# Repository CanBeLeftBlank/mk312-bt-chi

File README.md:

Welcome to the MK-312BTχ (Chi) project. This is a fork of the project bij [CrashOverride85](https://github.com/CrashOverride85/mk312-bt) which itself is cloned from an earlier project and ultimately a project by MetaFetish that has since been removed from GitHub.

# What is it?

MK-312BTχ is a DYI electronics kit to build an Estim box, including schematics, printed circuit board layouts and parts lists. If you don't know what an Estim box is or have no experience with electronics and soldering, this project is probably not for you...

If you do know what an Estim box is: build and use at your own risk! Even though a lot of people have build these devices there's always room for error and (painful) experiences.

## How is this different from the other cloned projects?

The original designs were made with the Eagle CAD software. Since I don't have an expensive Eagle license I decided to convert the schematics to the open source KiCad format. This will hopefully allow more people to experiment with this or improve the design.

There was also an update available of the schematic (v1.4) and final board design, but only as PDFs and images. So I compared them with the old v1.3 Eagle designs and re-applied the changes in the KiCad version. This is the original v1.4χ version.

Second, documentation was always a bit lacking or confusing. This project aims to improve on that.

And who knows, maybe in the future we'll have original source code and firmware as well...

## What's with the X in the version?

It's not an X but the Greek letter χ (Chi) which is pronounced 'Kai', similar to 'KiCad'. 

# Building!

So, let's get to the main event. There are 4 parts to this:

* Getting the circuit boards
* Buying the electronic parts
* Soldering and putting it together
* Programming the firmware

Oh yes, before you continue: you must be able to program an Atmel microcontroller or have someone who can do it for you. 

## Circuit boards (PCB)

In the gerbers/ folder are the latest Gerber files as zip files, one for each of the 3 boards: the main circuit board, the display print and the front panel. Easiest is to have these boards made at a PCB factory; the front panel looks best with a black soldermask.

The zip files contain Gerber files with Protel filenames; they are known to work with at least one PCB manufacturer (PCBWay: no affiliation or sponsorship). I would like some feedback on how it fares with other manufacturers.

## The electronic parts

*As of the time of writing (December 2022), there is still a global shortage of chips and other electronic parts. However, with a little bit of creativity you can still get all the parts. For example I substituted the main processor, an ATMega16A-PU, with the ATMega16L-8PU, a low-power version that runs 'only' at 8 MHz which so happens to be the actual clockspeed. The stereo pot at the display panel is no longer available at Mouser, but AliExpress has plenty of them. And the blue LCD that is originally specified is not shipped everywhere, so I picked a green one.*

In the bom_and_info/ folder is a spreadsheet with a parts-list for Mouser; a few substitutions / replacements have been marked with colors and notes. This list has been used to get parts in August 2022, but your milage may vary. There is no BOM for other parts suppliers, but all components are standard parts so it should be easy to find them. The BOM also contains a suitable case.

There is one choice you have to make: which transformer to use. The PCB supports two types: the Xicon 42TL004 (default) and the 42TU200. The latter is bigger and should give more power on the outputs, but was until recently only available in bulk. If you buy the 42TU200 you must use a lower value for R30; see the BOM for details.

You need a short ribbon cable to connect the display to the main board. The BOM lists separate components for this but you can also buy a pre-made 24-pin ribbon cable at Amazon, EBay or AliExpress.

## Building it

In the bom_and_info/ folder there is a document with detailed building instructions, as well as 2 PDFs with component placements for the display and mainboard. You will need a soldering iron with a fine tip, some thin solder (leaded or lead-free) and a bit of free time. All parts are through-hole so easy to mount. 

With the given PCBs and case you can mount the mainboard at the bottom of the case with a few short screws; the display with front panel slides in vertically (see the images). 

## Programming the firmware

This is a bit of a gray area. There are various firmware revisions floating around on the 'Net, sometimes with names like 'buttshock'; problem is they are only available as binary files, no sources. Some have patches and fixes to the original firmware but are still binary-only. 

This repository contains an old but working version of the firmware with tweaks for the chosen LCD; this has to do with the ← and → symbols on the LCD that differs between brands.

To set your programmer fuses:

* Low fuse: 0xFF
* High fuse: 0xDC

This assumes an 8 MHz crystal is used.

On the mainboard PCB is a 6-pin header for programming, compatible with the Atmel-ICE programmer (and probably a few others). An alternative is an external programmer. There is no way to upload the firmware using a bootloader AFAIK.

# Using it

## Charging

The recommende charging voltage is 15 Volt DC; the box monitors the input voltage and if it is too high, the firmware may display an error 21. The battery will still be charged to its nominal voltage but the LM2914 might get hot due to a high charging current.

Note: as with all estim boxes it is not recommend to use the machine while it is being charged and thus (indirectly) connected to mains voltage.

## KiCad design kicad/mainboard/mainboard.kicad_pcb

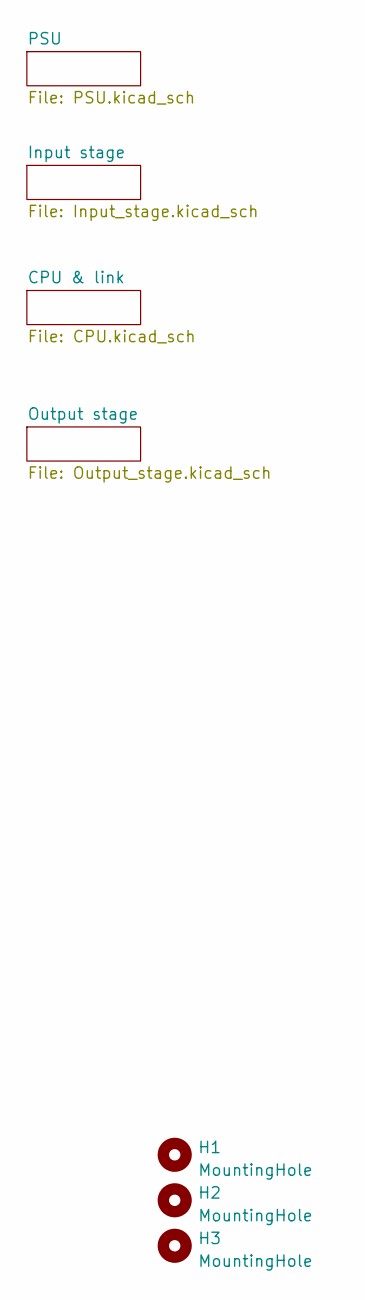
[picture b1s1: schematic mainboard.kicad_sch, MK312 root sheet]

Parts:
H1, H2, H3: MountingHole; MountingHole_2.5mm

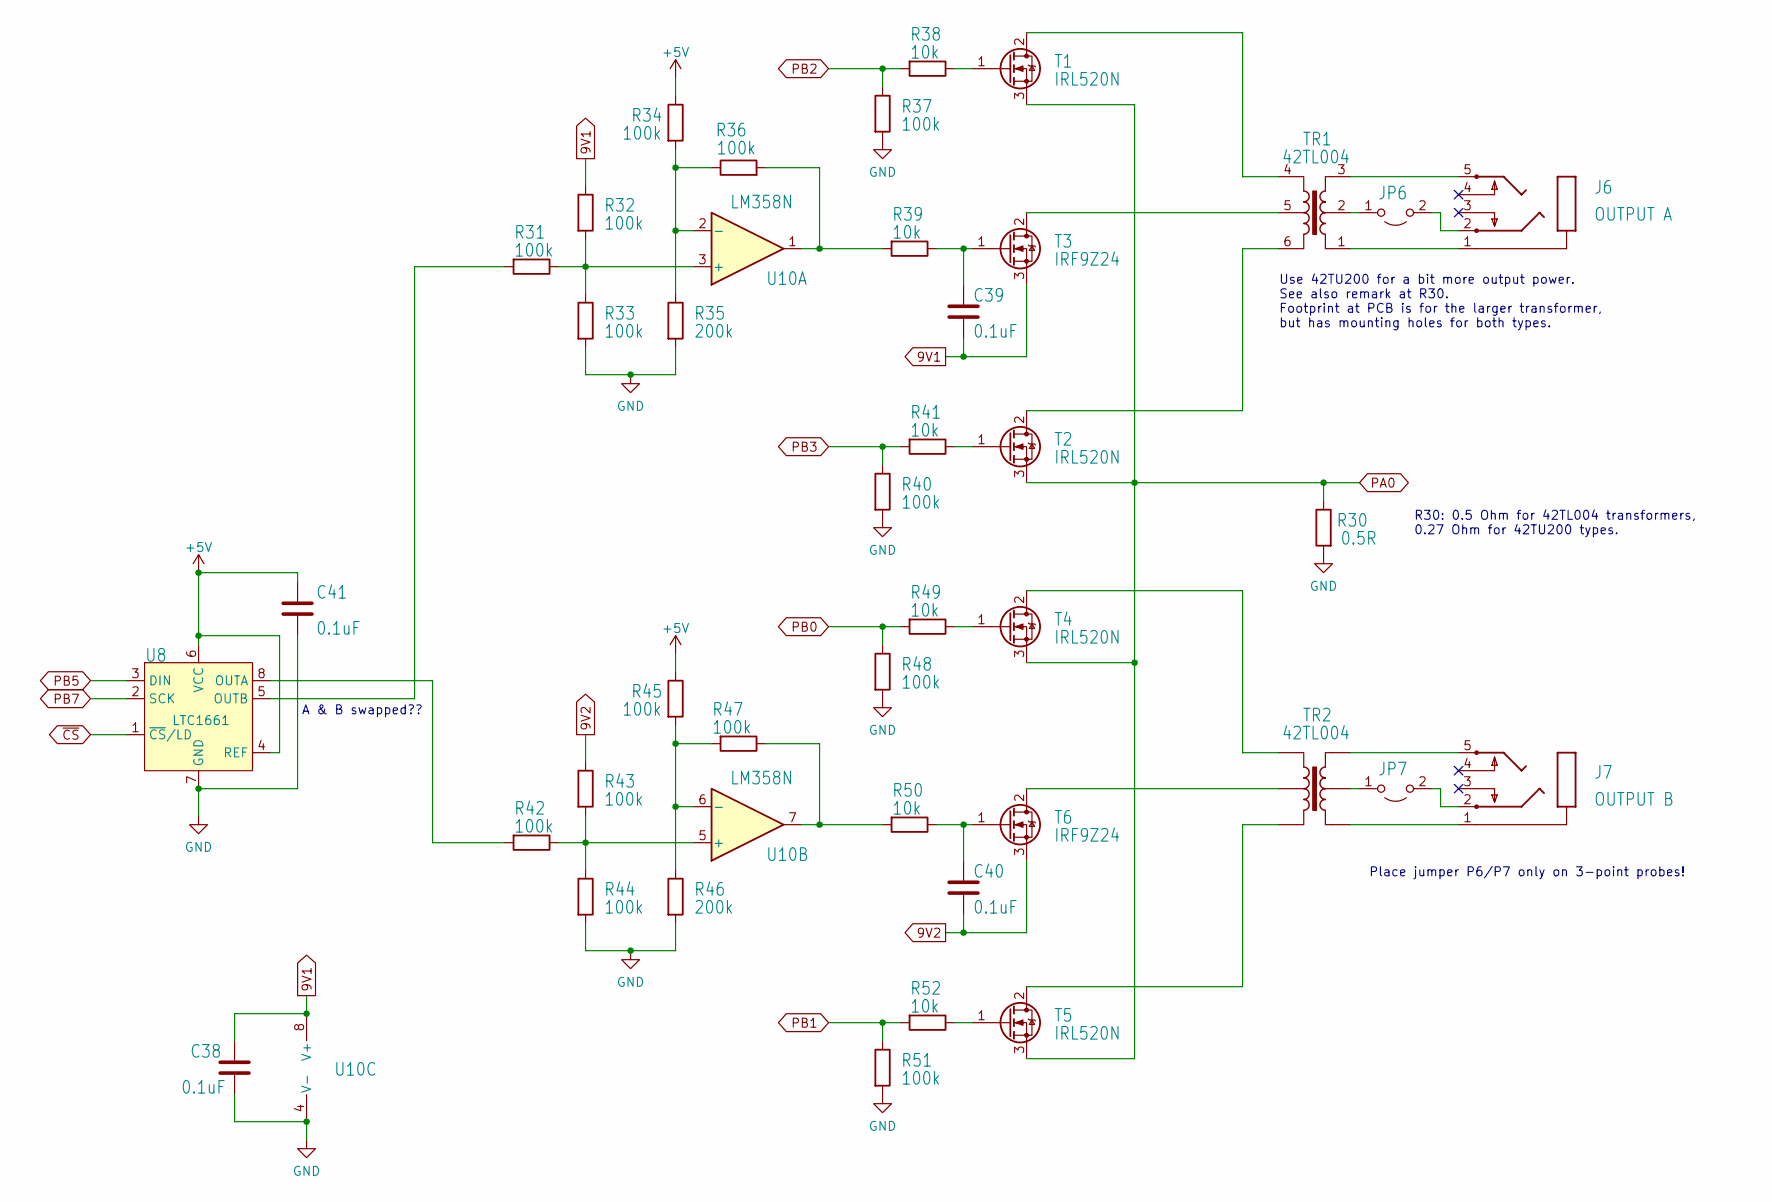
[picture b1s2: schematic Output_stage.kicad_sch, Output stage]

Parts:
C38, C39, C40, C41: 0.1uF; C_Disc_D3.0mm_W1.6mm_P2.50mm
J6: OUTPUT A; STX3100
J7: OUTPUT B; STX3100
JP6, JP7: JP1E; PinHeader_1x02_P2.54mm_Vertical
R30: 0.5R; R_Axial_DIN0309_L9.0mm_D3.2mm_P12.70mm_Horizontal
R31, R32, R33, R34, R36, R42, R43, R44, R45, R47: 100k; R_Axial_DIN0207_L6.3mm_D2.5mm_P10.16mm_Horizontal
R35, R46: 200k; R_Axial_DIN0207_L6.3mm_D2.5mm_P10.16mm_Horizontal
R37, R40, R48, R51: 100k; R_Axial_DIN0207_L6.3mm_D2.5mm_P2.54mm_Vertical
R38, R41, R49, R52: 10k; R_Axial_DIN0207_L6.3mm_D2.5mm_P2.54mm_Vertical
R39, R50: 10k; R_Axial_DIN0207_L6.3mm_D2.5mm_P10.16mm_Horizontal
T1, T2, T4, T5: IRL520N; TO-220-3_Vertical
T3, T6: IRF9Z24; TO-220-3_Vertical
TR1, TR2: 42TL004; Transformer_Xicon_42TL_42TU_Combi
U8: LTC1661; DIP-8_W7.62mm
U10: LM358N; DIP-8_W7.62mm

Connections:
9V1: C38.1, C39.2, R32.1, T3.3 (S), U10.8 (V+); also elsewhere on the board
9V2: C40.2, R43.1, T6.3 (S); also elsewhere on the board
+5V: C41.1, R34.1, R45.1, U8.4 (REF), U8.6 (VCC); also elsewhere on the board
GND: C38.2, C41.2, R30.2, R33.2, R35.2, R37.2, R40.2, R44.2, R46.2, R48.2, R51.2, U8.7 (GND), U10.4 (V-); also elsewhere on the board
unnamed: C39.1, R39.1, T3.1 (G)
unnamed: C40.1, R50.1, T6.1 (G)
unnamed: J6.1, TR1.1
unnamed: J6.2, JP6.2 (B)
unnamed: J6.5, TR1.3
unnamed: J7.1, TR2.1
unnamed: J7.2, JP7.2 (B)
unnamed: J7.5, TR2.3
unnamed: JP6.1 (A), TR1.2
unnamed: JP7.1 (A), TR2.2
unnamed: R31.1, R32.2, R33.1, U10.3 (+)
unnamed: R31.2, U8.5 (OUTB)
unnamed: R34.2, R35.1, R36.1, U10.2 (-)
unnamed: R36.2, R39.2, U10.1
unnamed: R38.1, T1.1 (G)
unnamed: R41.1, T2.1 (G)
unnamed: R42.1, R43.2, R44.1, U10.5 (+)
unnamed: R42.2, U8.8 (OUTA)
unnamed: R45.2, R46.1, R47.2, U10.6 (-)
unnamed: R47.1, R50.2, U10.7
unnamed: R49.1, T4.1 (G)
unnamed: R52.1, T5.1 (G)
unnamed: T1.2 (D), TR1.4
unnamed: T2.2 (D), TR1.6
unnamed: T3.2 (D), TR1.5
unnamed: T4.2 (D), TR2.4
unnamed: T5.2 (D), TR2.6
unnamed: T6.2 (D), TR2.5
PA0: R30.1, T1.3 (S), T2.3 (S), T4.3 (S), T5.3 (S); also elsewhere on the board
PB0: R48.1, R49.2; also elsewhere on the board
PB1: R51.1, R52.2; also elsewhere on the board
PB2: R37.1, R38.2; also elsewhere on the board
PB3: R40.1, R41.2; also elsewhere on the board
PB5: U8.3 (DIN); also elsewhere on the board
PB7: U8.2 (SCK); also elsewhere on the board
~CS: U8.1 (~CS/LD); also elsewhere on the board

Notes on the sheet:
A & B swapped??
R30: 0.5 Ohm for 42TL004 transformers, 0.27 Ohm for 42TU200 types.
Use 42TU200 for a bit more output power. See also remark at R30. Footprint at PCB is for the larger transformer, but has mounting holes for both types.
Place jumper P6/P7 only on 3-point probes!

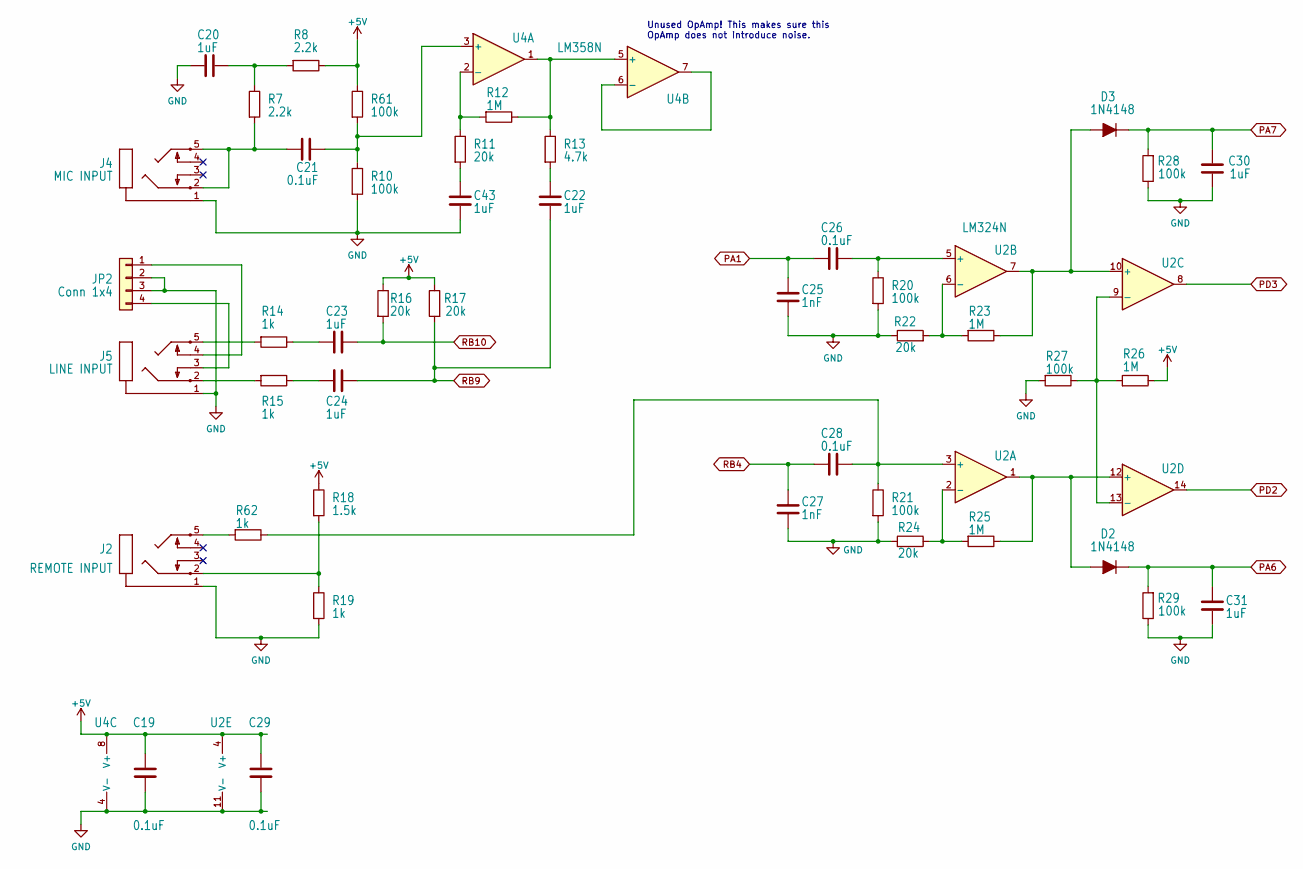
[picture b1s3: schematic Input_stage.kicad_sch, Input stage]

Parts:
C19, C21, C26, C28, C29: 0.1uF; C_Disc_D3.0mm_W1.6mm_P2.50mm
C20, C22, C23, C24, C30, C31, C43: 1uF; C_Disc_D3.4mm_W2.1mm_P2.50mm
C25, C27: 1nF; C_Disc_D3.0mm_W1.6mm_P2.50mm
D2, D3: 1N4148; D_DO-35_SOD27_P10.16mm_Horizontal
J2: REMOTE INPUT; STX3100
J4: MIC INPUT; STX3100
J5: LINE INPUT; STX3100
JP2: Conn 1x4; PinHeader_1x04_P2.54mm_Vertical
R7, R8: 2.2k; R_Axial_DIN0207_L6.3mm_D2.5mm_P10.16mm_Horizontal
R10, R20, R21, R27, R28, R29, R61: 100k; R_Axial_DIN0207_L6.3mm_D2.5mm_P10.16mm_Horizontal
R11, R16, R17, R22, R24: 20k; R_Axial_DIN0207_L6.3mm_D2.5mm_P10.16mm_Horizontal
R12, R23, R25, R26: 1M; R_Axial_DIN0207_L6.3mm_D2.5mm_P10.16mm_Horizontal
R13: 4.7k; R_Axial_DIN0207_L6.3mm_D2.5mm_P10.16mm_Horizontal
R14, R15, R19, R62: 1k; R_Axial_DIN0207_L6.3mm_D2.5mm_P10.16mm_Horizontal
R18: 1.5k; R_Axial_DIN0207_L6.3mm_D2.5mm_P10.16mm_Horizontal
U2: LM324N; DIP-14_W7.62mm
U4: LM358N; DIP-8_W7.62mm

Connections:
+5V: C19.1, C29.1, R8.1, R16.1, R17.1, R18.1, R26.1, R61.1, U2.4 (V+), U4.8 (V+); also elsewhere on the board
GND: C19.2, C20.2, C25.1, C27.1, C29.2, C30.1, C31.2, C43.2, J2.1, J4.1, J5.1, JP2.2, JP2.3, R10.2, R19.2, R20.2, R21.2, R22.1, R24.2, R27.2, R28.1, R29.1, U2.11 (V-), U4.4 (V-); also elsewhere on the board
unnamed: C20.1, R7.1, R8.2
unnamed: C21.1, J4.2, J4.5, R7.2
unnamed: C21.2, R10.1, R61.2, U4.3 (+)
unnamed: C22.1, R13.2
unnamed: C23.2, R14.1
unnamed: C24.2, R15.1
unnamed: C26.1, R20.1, U2.5 (+)
unnamed: C28.1, R21.1, R62.1, U2.3 (+)
unnamed: C43.1, R11.2
unnamed: D2.2 (A), R25.1, U2.1, U2.12 (+)
unnamed: D3.2 (A), R23.1, U2.7, U2.10 (+)
unnamed: J2.2, R18.2, R19.1
unnamed: J2.5, R62.2
unnamed: J5.2, R15.2
unnamed: J5.3, JP2.4
unnamed: J5.4, JP2.1
unnamed: J5.5, R14.2
unnamed: R11.1, R12.2, U4.2 (-)
unnamed: R12.1, R13.1, U4.1, U4.5 (+)
unnamed: R22.2, R23.2, U2.6 (-)
unnamed: R24.1, R25.2, U2.2 (-)
unnamed: R26.2, R27.1, U2.9 (-), U2.13 (-)
unnamed: U4.6 (-), U4.7
PA1: C25.2, C26.2; also elsewhere on the board
PA6: C31.1, D2.1 (K), R29.2; also elsewhere on the board
PA7: C30.2, D3.1 (K), R28.2; also elsewhere on the board
PD2: U2.14; also elsewhere on the board
PD3: U2.8; also elsewhere on the board
RB4: C27.2, C28.2; also elsewhere on the board
RB9: C22.2, C24.1, R17.2; also elsewhere on the board
RB10: C23.1, R16.2; also elsewhere on the board

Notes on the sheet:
Unused OpAmp! This makes sure this OpAmp does not introduce noise.

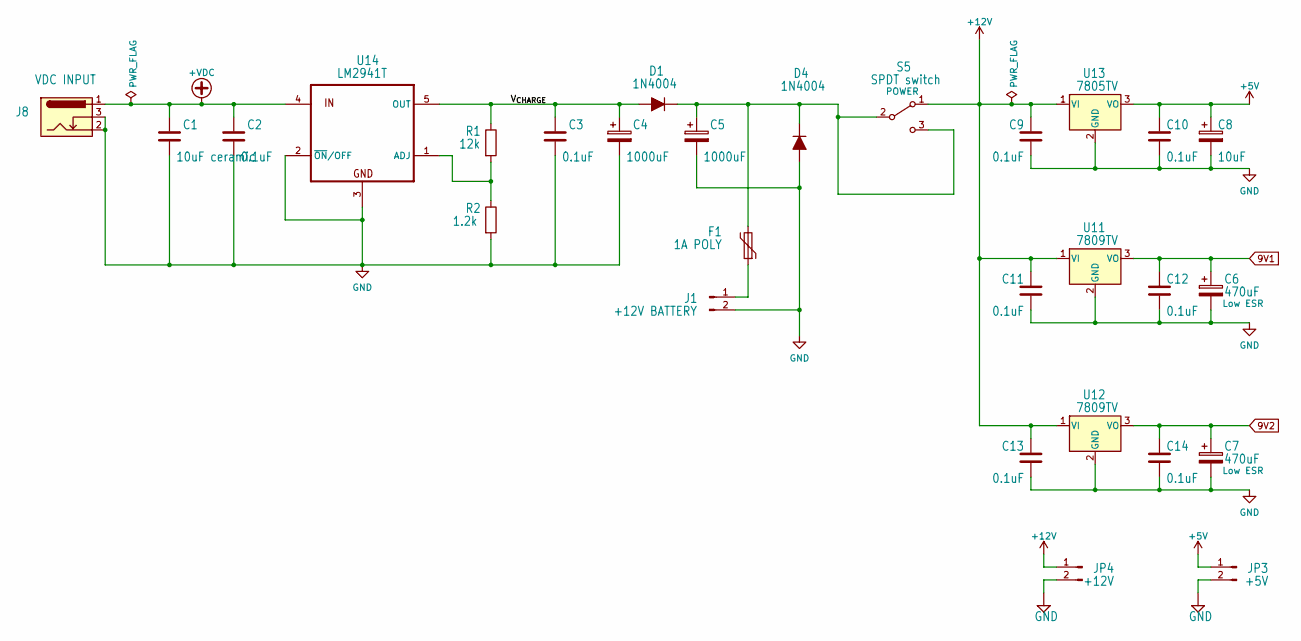
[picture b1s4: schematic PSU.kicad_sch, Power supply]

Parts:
C1: 10uF ceramic; C_Disc_D5.0mm_W2.5mm_P2.50mm
C2, C3, C9, C10, C11, C12, C13, C14: 0.1uF; C_Disc_D3.0mm_W1.6mm_P2.50mm
C4, C5: 1000uF; CP_Radial_D10.0mm_P5.00mm
C6, C7: 470uF; CP_Radial_D8.0mm_P3.50mm
C8: 10uF; CP_Radial_D6.3mm_P2.50mm
D1, D4: 1N4004; D_DO-41_SOD81_P10.16mm_Horizontal
F1: 1A POLY; Fuse_Littelfuse-LVR100
J1: +12V BATTERY; DEANS
J8: VDC INPUT; BarrelJack_GCT_DCJ200-10-A_Horizontal
JP3: +5V; PinHeader_1x02_P2.54mm_Vertical
JP4: +12V; PinHeader_1x02_P2.54mm_Vertical
R1: 12k; R_Axial_DIN0207_L6.3mm_D2.5mm_P10.16mm_Horizontal
R2: 1.2k; R_Axial_DIN0207_L6.3mm_D2.5mm_P10.16mm_Horizontal
S5: SPDT switch; LPV-1
U11, U12: 7809TV; TO-220-3_Vertical
U13: 7805TV; TO-220-3_Vertical
U14: LM2941T; TO-220-5_P3.4x3.7mm_StaggerOdd_Lead3.8mm_Vertical

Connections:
9V1: C6.1, C12.1, U11.3 (VO); also elsewhere on the board
9V2: C7.1, C14.1, U12.3 (VO); also elsewhere on the board
+5V: C8.1, C10.1, JP3.1, U13.3 (VO); also elsewhere on the board
+12V: C9.1, C11.1, C13.1, JP4.1, S5.1 (A), U11.1 (VI), U12.1 (VI), U13.1 (VI); also elsewhere on the board
+VDC: C1.1, C2.1, J8.1, U14.4 (IN); also elsewhere on the board
/PSU/V_{CHARGE}: C3.1, C4.1, D1.2 (A), R1.1, U14.5 (OUT)
GND: C1.2, C2.2, C3.2, C4.2, C5.2, C6.2, C7.2, C8.2, C9.2, C10.2, C11.2, C12.2, C13.2, C14.2, D4.2 (A), J1.2, J8.2, J8.3, JP3.2, JP4.2, R2.2, U11.2 (GND), U12.2 (GND), U13.2 (GND), U14.2 (~ON/OFF), U14.3 (GND); also elsewhere on the board
unnamed: C5.1, D1.1 (K), D4.1 (K), F1.2, S5.2 (B), S5.3 (C)
unnamed: F1.1, J1.1
unnamed: R1.2, R2.1, U14.1 (ADJ)

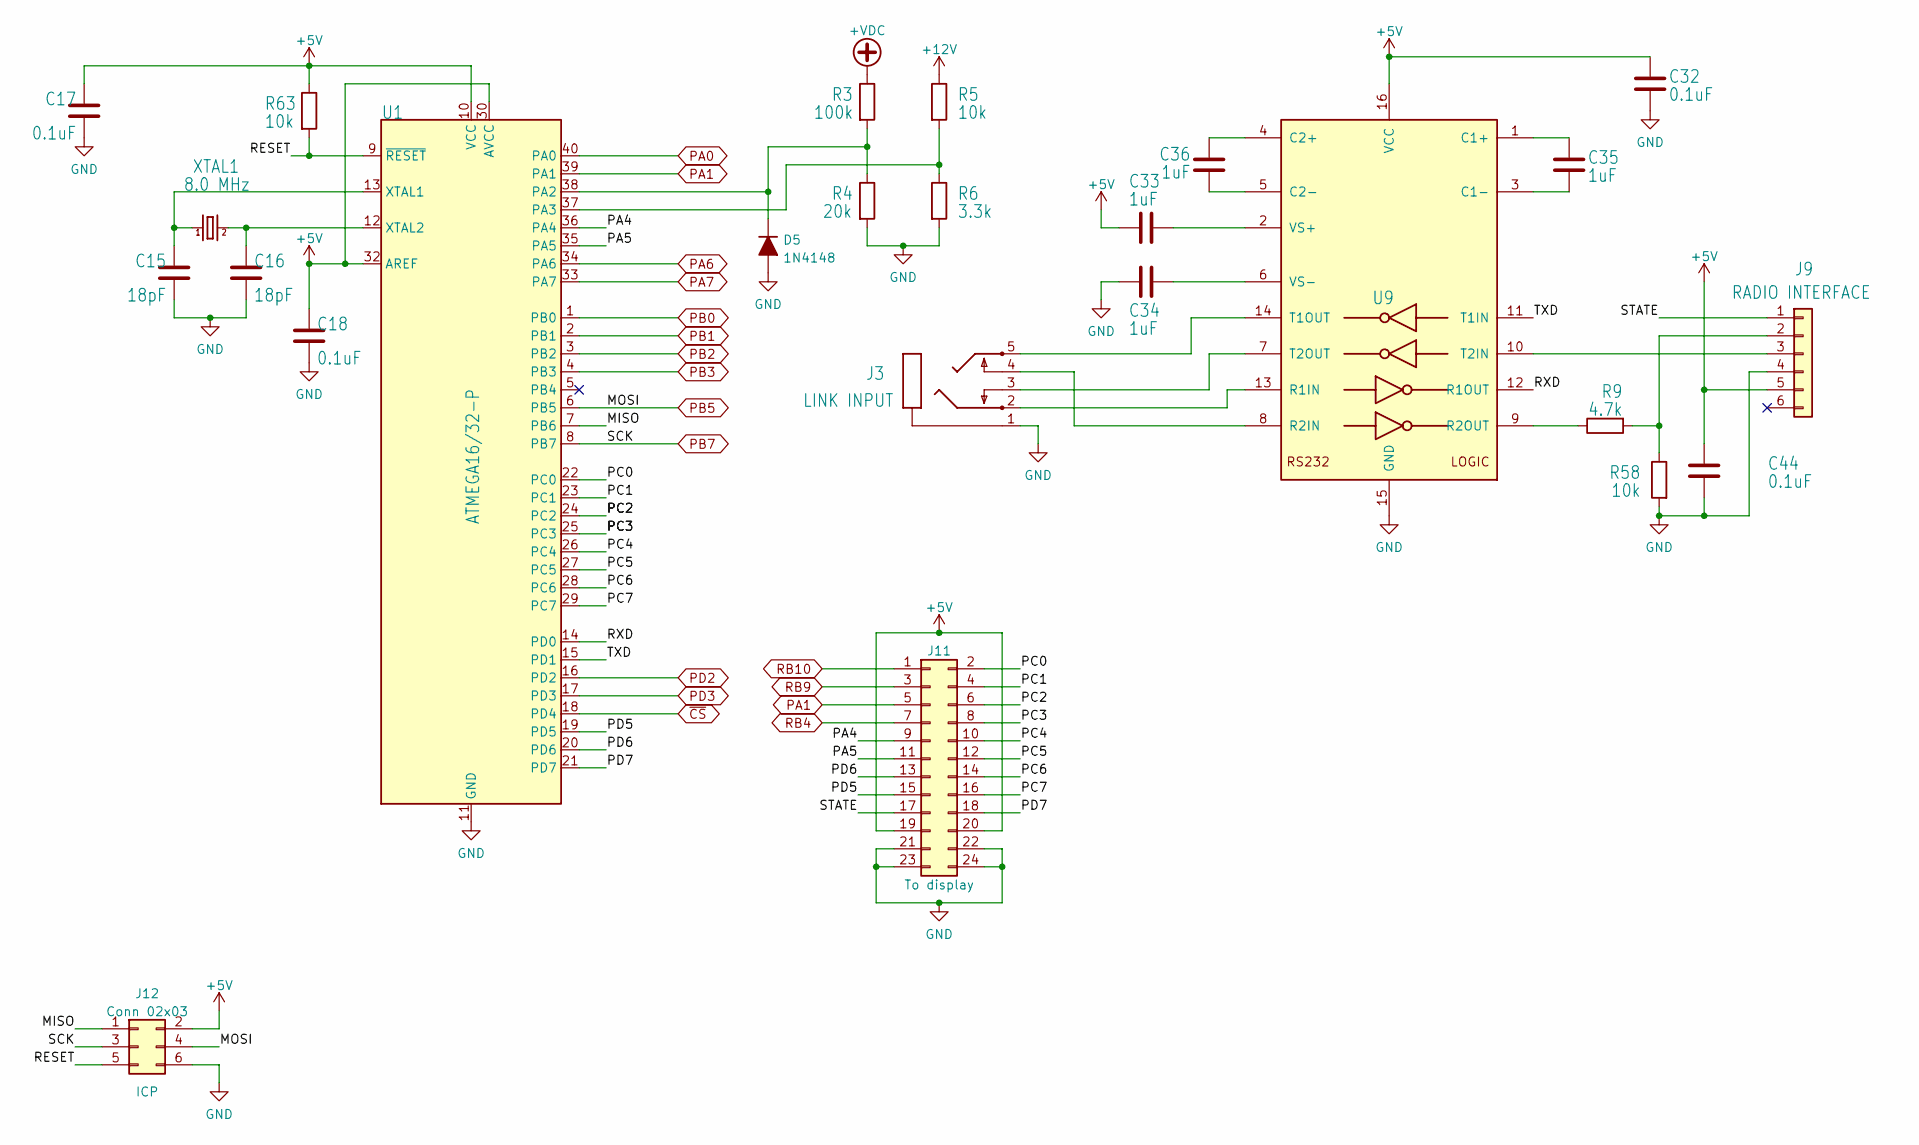
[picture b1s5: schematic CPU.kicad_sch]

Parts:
C15, C16: 18pF; C_Disc_D3.0mm_W1.6mm_P2.50mm
C17, C18, C32, C44: 0.1uF; C_Disc_D3.0mm_W1.6mm_P2.50mm
C33, C34, C35, C36: 1uF; C_Disc_D3.4mm_W2.1mm_P2.50mm
D5: 1N4148; D_DO-35_SOD27_P10.16mm_Horizontal
J3: LINK INPUT; STX3100
J9: RADIO INTERFACE; PinHeader_1x06_P2.54mm_Vertical
J11: Conn_02x12; IDC-Header_2x12_P2.54mm_Vertical
J12: Conn 02x03; IDC-Header_2x03_P2.54mm_Vertical
R3: 100k; R_Axial_DIN0207_L6.3mm_D2.5mm_P10.16mm_Horizontal
R4: 20k; R_Axial_DIN0207_L6.3mm_D2.5mm_P10.16mm_Horizontal
R5, R58, R63: 10k; R_Axial_DIN0207_L6.3mm_D2.5mm_P10.16mm_Horizontal
R6: 3.3k; R_Axial_DIN0207_L6.3mm_D2.5mm_P10.16mm_Horizontal
R9: 4.7k; R_Axial_DIN0207_L6.3mm_D2.5mm_P10.16mm_Horizontal
U1: ATMEGA16/32-P; DIP-40_W15.24mm
U9: MAX232; DIP-16_W7.62mm
XTAL1: 8.0 MHz; Crystal_HC49-U_Vertical

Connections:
+5V: C17.1, C18.1, C32.1, C33.2, C44.1, J9.5, J11.19, J11.20, J12.2, R63.1, U1.10 (VCC), U1.30 (AVCC), U1.32 (AREF), U9.16 (VCC); also elsewhere on the board
+12V: R5.1; also elsewhere on the board
+VDC: R3.1; also elsewhere on the board
/CPU & link/MISO: J12.1, U1.7 (PB6)
/CPU & link/PA4: J11.9, U1.36 (PA4)
/CPU & link/PA5: J11.11, U1.35 (PA5)
/CPU & link/PC0: J11.2, U1.22 (PC0)
/CPU & link/PC1: J11.4, U1.23 (PC1)
/CPU & link/PC2: J11.6, U1.24 (PC2)
/CPU & link/PC3: J11.8, U1.25 (PC3)
/CPU & link/PC4: J11.10, U1.26 (PC4)
/CPU & link/PC5: J11.12, U1.27 (PC5)
/CPU & link/PC6: J11.14, U1.28 (PC6)
/CPU & link/PC7: J11.16, U1.29 (PC7)
/CPU & link/PD5: J11.15, U1.19 (PD5)
/CPU & link/PD6: J11.13, U1.20 (PD6)
/CPU & link/PD7: J11.18, U1.21 (PD7)
/CPU & link/RESET: J12.5, R63.2, U1.9 (~RESET)
/CPU & link/RXD: U1.14 (PD0), U9.12 (R1OUT)
/CPU & link/STATE: J9.1, J11.17
/CPU & link/TXD: U1.15 (PD1), U9.11 (T1IN)
GND: C15.2, C16.2, C17.2, C18.2, C32.2, C34.2, C44.2, D5.2 (A), J3.1, J9.4, J11.21, J11.22, J11.23, J11.24, J12.6, R4.2, R6.2, R58.2, U1.11 (GND), U1.31 (GND), U9.15 (GND); also elsewhere on the board
unnamed: C15.1, U1.13 (XTAL1), XTAL1.1
unnamed: C16.1, U1.12 (XTAL2), XTAL1.2
unnamed: C33.1, U9.2 (VS+)
unnamed: C34.1, U9.6 (VS-)
unnamed: C35.1, U9.1 (C1+)
unnamed: C35.2, U9.3 (C1-)
unnamed: C36.1, U9.5 (C2-)
unnamed: C36.2, U9.4 (C2+)
unnamed: D5.1 (K), R3.2, R4.1, U1.38 (PA2)
unnamed: J3.2, U9.13 (R1IN)
unnamed: J3.3, U9.7 (T2OUT)
unnamed: J3.4, U9.8 (R2IN)
unnamed: J3.5, U9.14 (T1OUT)
unnamed: J9.2, R9.2, R58.1
unnamed: J9.3, U9.10 (T2IN)
unnamed: R5.2, R6.1, U1.37 (PA3)
unnamed: R9.1, U9.9 (R2OUT)
PA0: U1.40 (PA0); also elsewhere on the board
PA1: J11.5, U1.39 (PA1); also elsewhere on the board
PA6: U1.34 (PA6); also elsewhere on the board
PA7: U1.33 (PA7); also elsewhere on the board
PB0: U1.1 (PB0); also elsewhere on the board
PB1: U1.2 (PB1); also elsewhere on the board
PB2: U1.3 (PB2); also elsewhere on the board
PB3: U1.4 (PB3); also elsewhere on the board
PB5: J12.4, U1.6 (PB5); also elsewhere on the board
PB7: J12.3, U1.8 (PB7); also elsewhere on the board
PD2: U1.16 (PD2); also elsewhere on the board
PD3: U1.17 (PD3); also elsewhere on the board
RB4: J11.7; also elsewhere on the board
RB9: J11.3; also elsewhere on the board
RB10: J11.1; also elsewhere on the board
~CS: U1.18 (PD4); also elsewhere on the board

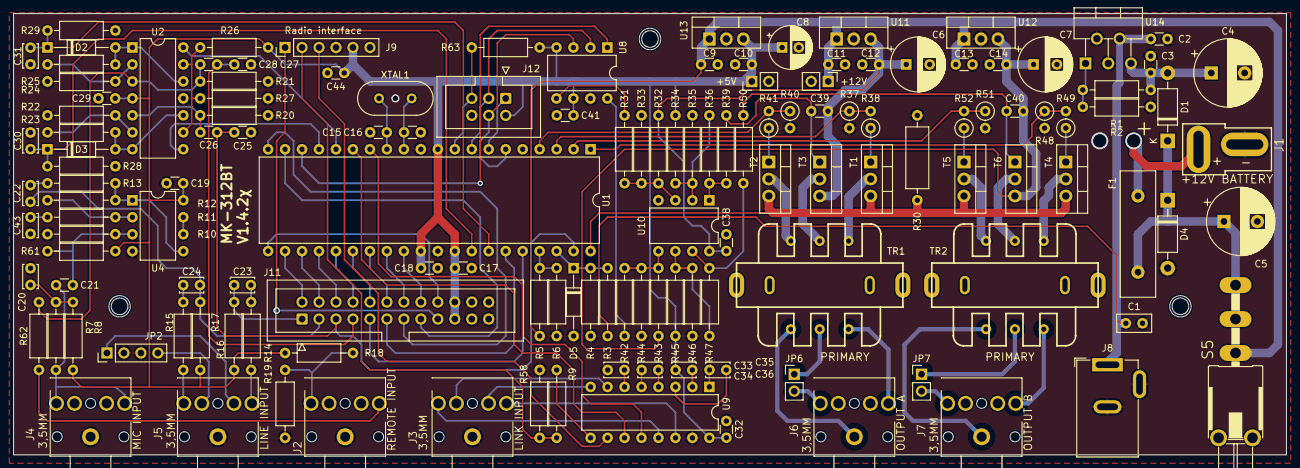
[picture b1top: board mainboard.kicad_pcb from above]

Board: 2 copper layers, 190.5 x 66.0 mm, 146 parts (0 on the bottom side), 112 nets.

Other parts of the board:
@HOLE0, @HOLE1, @HOLE4: (no value)

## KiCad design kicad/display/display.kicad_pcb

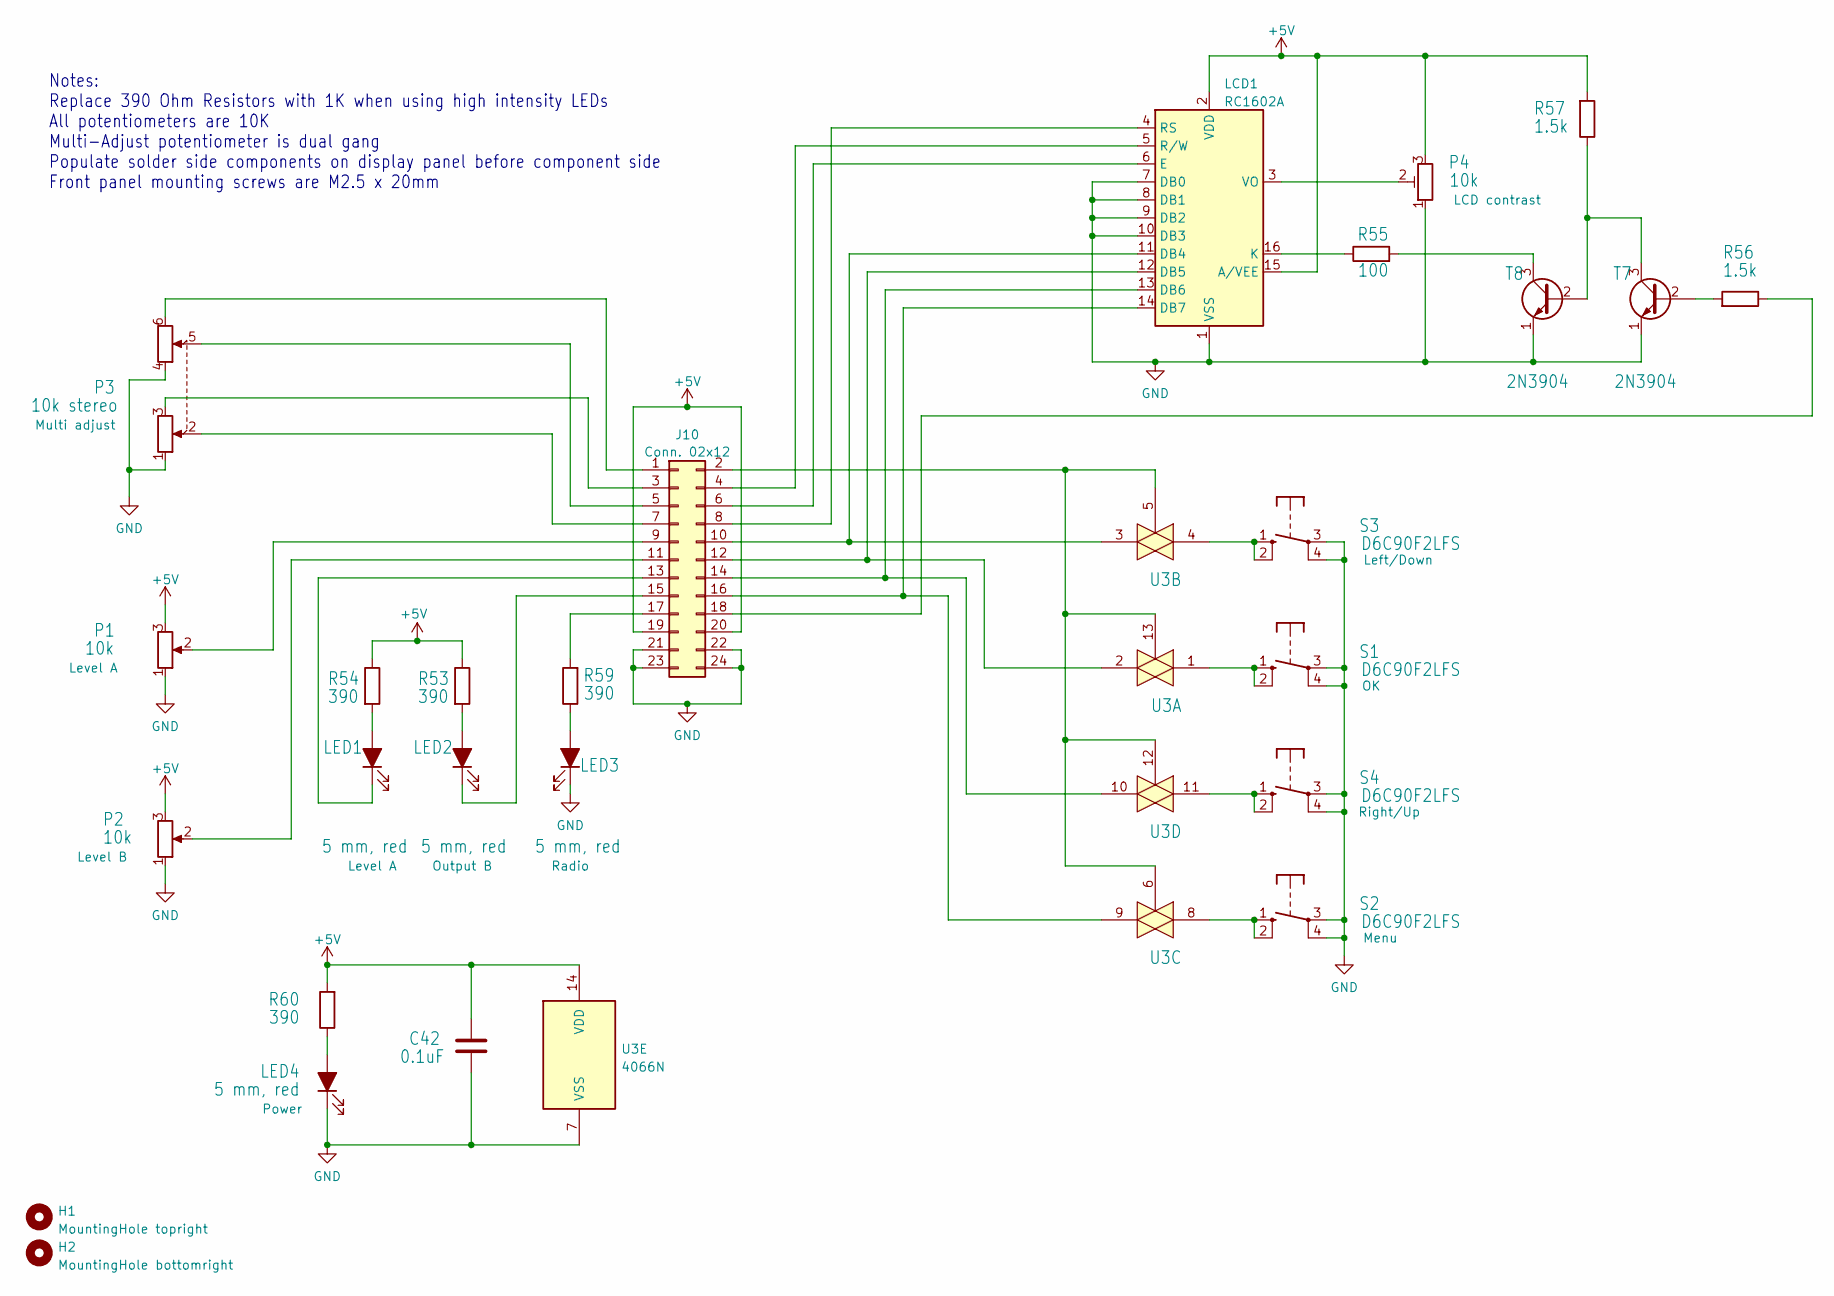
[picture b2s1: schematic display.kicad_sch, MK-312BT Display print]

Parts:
C42: 0.1uF; C_Disc_D3.4mm_W2.1mm_P2.50mm
H1: MountingHole topright; MountingHole_2.5mm
H2: MountingHole bottomright; MountingHole_2.5mm
J10: Conn. 02x12; IDC-Header_2x12_P2.54mm_Vertical
LCD1: RC1602A; WC1602A
LED1, LED2, LED3, LED4: 5 mm, red; LED_D5.0mm
P1, P2: 10k; Potentiometer_Alps_RK09L_Single_Vertical
P3: 10k stereo; Potentiometer_Alps_RK09L_Double_Vertical
P4: 10k; B25P
R53, R54, R59, R60: 390; R_Axial_DIN0207_L6.3mm_D2.5mm_P10.16mm_Horizontal
R55: 100; R_Axial_DIN0207_L6.3mm_D2.5mm_P10.16mm_Horizontal
R56, R57: 1.5k; R_Axial_DIN0207_L6.3mm_D2.5mm_P10.16mm_Horizontal
S1, S2, S3, S4: D6C90F2LFS; DTE6K
T7, T8: 2N3904; TO-92_Inline
U3: 4066N; DIP-14_W7.62mm

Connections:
+5V: C42.1, J10.19, J10.20, LCD1.2 (VDD), LCD1.15 (A/VEE), P1.3, P2.3, P4.3, R53.1, R54.1, R57.2, R60.2, U3.14 (VDD)
GND: C42.2, J10.21, J10.22, J10.23, J10.24, LCD1.1 (VSS), LCD1.7 (DB0), LCD1.8 (DB1), LCD1.9 (DB2), LCD1.10 (DB3), LED3.1 (K), LED4.1 (K), P1.1, P2.1, P3.1, P3.4, P4.1, S1.3, S1.4 (P@1), S2.3, S2.4 (P@1), S3.3, S3.4 (P@1), S4.3, S4.4 (P@1), T7.1 (E), T8.1 (E), U3.7 (VSS)
unnamed: J10.1, P3.6
unnamed: J10.2, U3.5, U3.6, U3.12, U3.13
unnamed: J10.3, P3.3
unnamed: J10.4, LCD1.5 (R/W)
unnamed: J10.5, P3.5
unnamed: J10.6, LCD1.6 (E)
unnamed: J10.7, P3.2
unnamed: J10.8, LCD1.4 (RS)
unnamed: J10.9, P1.2
unnamed: J10.10, LCD1.11 (DB4), U3.3
unnamed: J10.11, P2.2
unnamed: J10.12, LCD1.12 (DB5), U3.2
unnamed: J10.13, LED1.1 (K)
unnamed: J10.14, LCD1.13 (DB6), U3.10
unnamed: J10.15, LED2.1 (K)
unnamed: J10.16, LCD1.14 (DB7), U3.9
unnamed: J10.17, R59.2
unnamed: J10.18, R56.1
unnamed: LCD1.3 (VO), P4.2
unnamed: LCD1.16 (K), R55.1
unnamed: LED1.2 (A), R54.2
unnamed: LED2.2 (A), R53.2
unnamed: LED3.2 (A), R59.1
unnamed: LED4.2 (A), R60.1
unnamed: R55.2, T8.3 (C)
unnamed: R56.2, T7.2 (B)
unnamed: R57.1, T7.3 (C), T8.2 (B)
unnamed: S1.1 (S), S1.2 (S@1), U3.1
unnamed: S2.1 (S), S2.2 (S@1), U3.8
unnamed: S3.1 (S), S3.2 (S@1), U3.4
unnamed: S4.1 (S), S4.2 (S@1), U3.11

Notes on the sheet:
Notes: Replace 390 Ohm Resistors with 1K when using high intensity LEDs All potentiometers are 10K Multi-Adjust potentiometer is dual gang Populate solder side components on display panel before component side Front panel mounting screws are M2.5 x 20mm

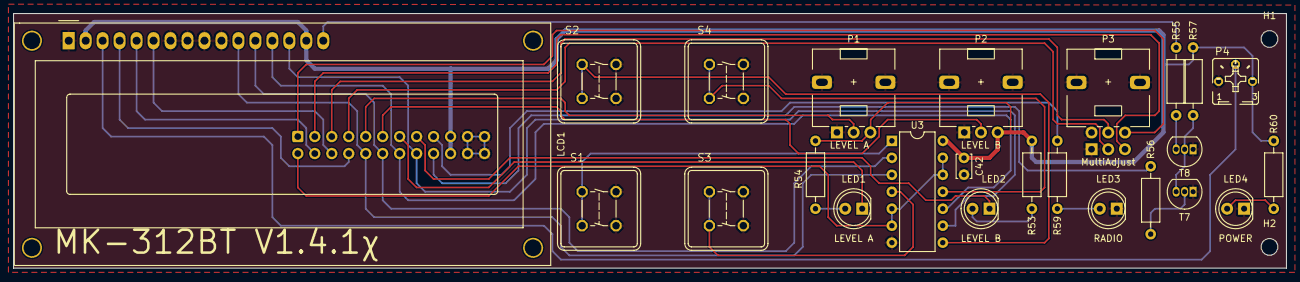
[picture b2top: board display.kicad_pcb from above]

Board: 2 copper layers, 190.5 x 38.1 mm, 27 parts (1 on the bottom side), 33 nets.
